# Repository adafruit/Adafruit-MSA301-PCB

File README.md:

## Adafruit MSA301 Triple Axis Accelerometer PCB

<a href="http://www.adafruit.com/products/4344"><br/>
Click here to purchase one from the Adafruit shop</a>

PCB files for the Adafruit MSA301 Triple Axis Accelerometer. 

Format is EagleCAD schematic and board layout
* https://www.adafruit.com/product/4344

### Description

The MSA301 is a super small and low cost **triple-axis accelerometer**. It's inexpensive, but has just about every 'extra' you'd want in an accelerometer:

* Three axis sensing, 14-bit resolution
* ±2g/±4g/±8g/±16g selectable scaling
* I2C interface on fixed I2C address 0x26
* Interrupt output
* Multiple data rate options 1 Hz to 500 Hz
* As low as 2uA current draw in low power mode (just the chip itself, not including any supporting circuitry)
* Tap, Double-tap, orientation & freefall detection
To make life easier so you can focus on your important work, we've taken the MSA301 and put it onto a breakout PCB along with support circuitry to let you use this little wonder with 3.3V (Feather/Raspberry Pi) or 5V (Arduino/ Metro328) logic levels. Additionally since it speaks I2C you can easily connect it up with two wires (plus power and ground!).  We've even included [SparkFun qwiic](https://www.sparkfun.com/qwiic) compatible [STEMMA QT](https://learn.adafruit.com/introducing-adafruit-stemma-qt) connectors for the I2C bus so **you don't even need to solder!** Just wire up to your favorite micro and you can use our [CircuitPython/Python](https://github.com/adafruit/Adafruit_CircuitPython_MSA301) or [Arduino drivers](https://github.com/adafruit/Adafruit_MSA301] to easily interface with the MSA301 and get motion measurements ASAP.

### License

Adafruit invests time and resources providing this open source design, please support Adafruit and open-source hardware by purchasing products from [Adafruit](https://www.adafruit.com)!

Designed by Limor Fried/Ladyada for Adafruit Industries.

Creative Commons Attribution/Share-Alike, all text above must be included in any redistribution. 
See license.txt for additional details.

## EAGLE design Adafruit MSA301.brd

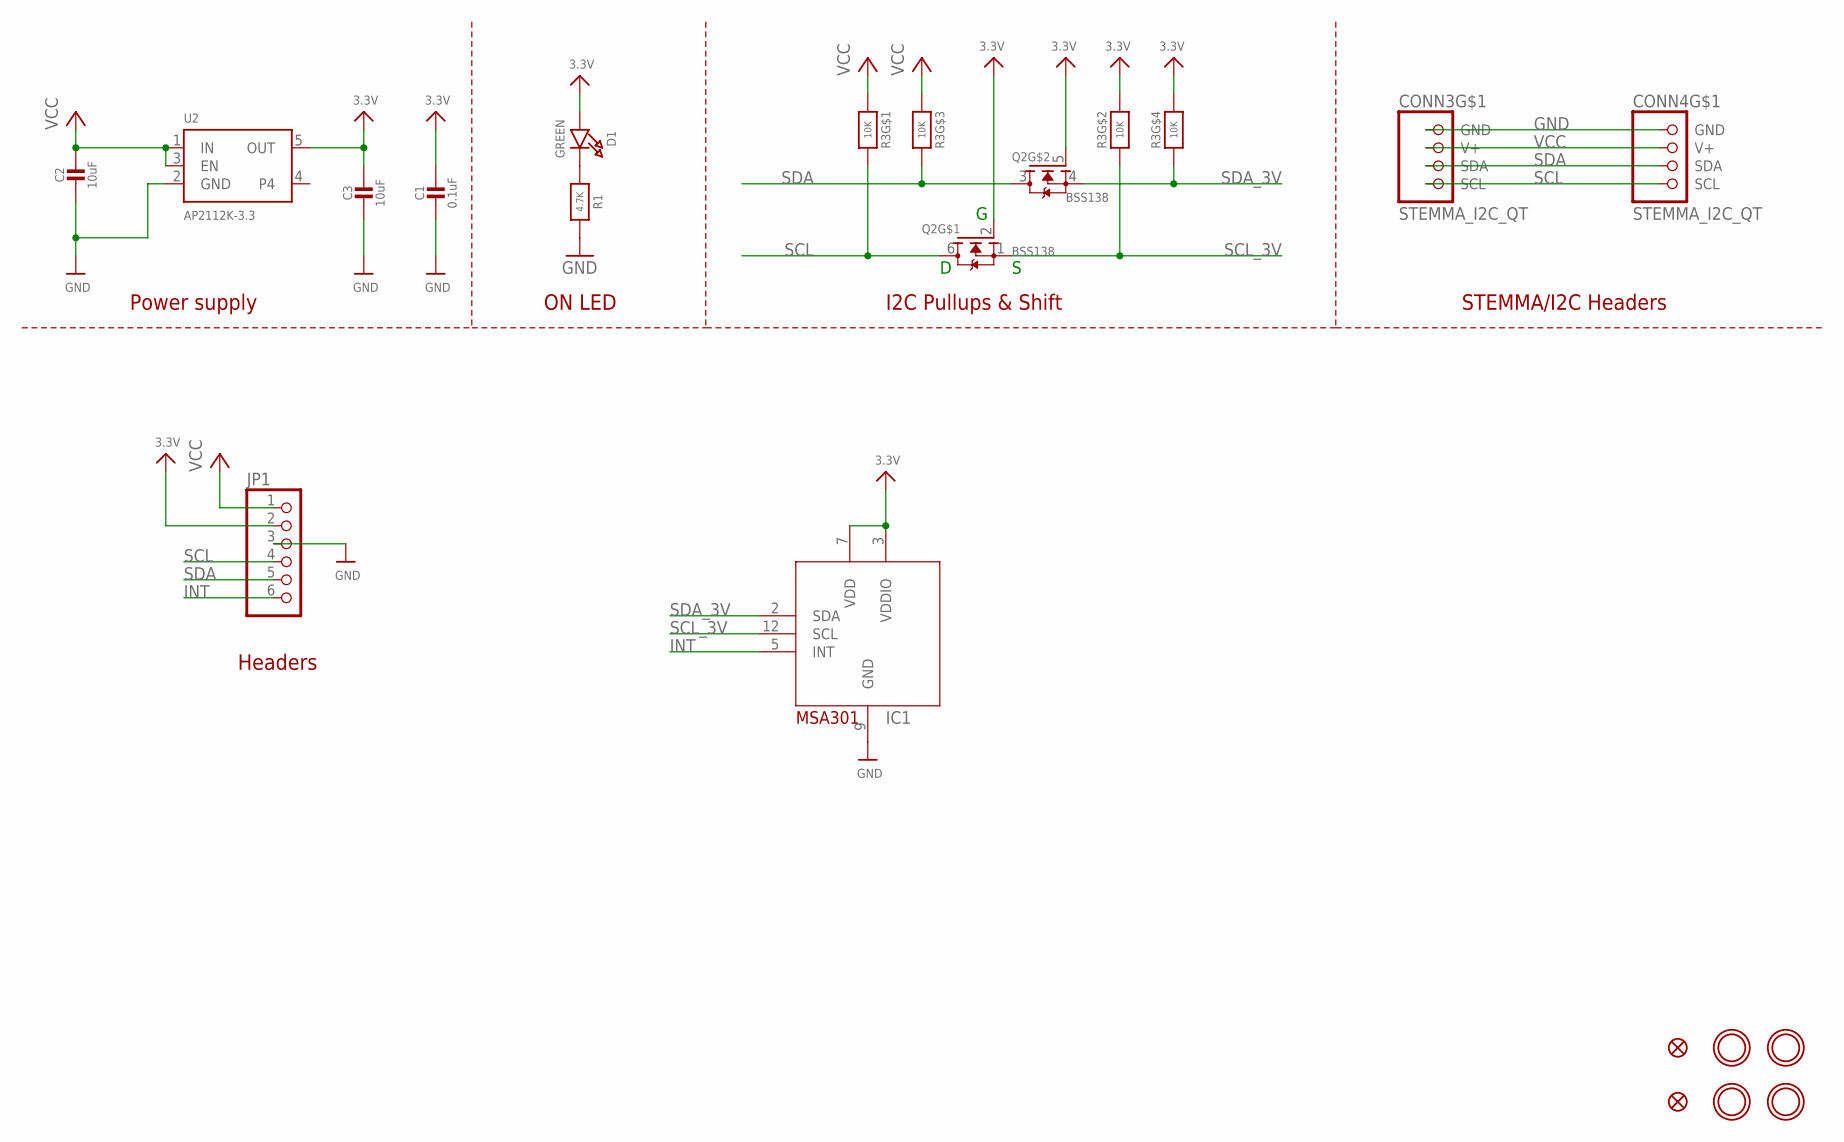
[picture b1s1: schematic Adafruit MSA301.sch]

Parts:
C1: 0.1uF; 0603-NO
C2, C3: 10uF; 0805-NO
CONN3, CONN4: STEMMA_I2C_QT; JST_SH4
D1: GREEN; CHIPLED_0603_NOOUTLINE
FID3, FID4: FIDUCIAL_1MM
IC1: MSA301; LGA12_2X2MM
JP1: HEADER-1X670MIL; 1X06_ROUND_70
Q2: BSS138; SOT363
R1: 4.7K; 0603-NO
R3: 10K; RESPACK_4X0603
U2: AP2112K-3.3; SOT23-5
U$1, U$17, U$19, U$21: MOUNTINGHOLE2.5; MOUNTINGHOLE_2.5_PLATED

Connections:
3.3V: C1.1, C3.1, D1.A, IC1.3 (VDDIO), IC1.7 (VDD), JP1.2, Q2.2 (G), Q2.5 (G), R3.2 (1), R3.4 (1), U2.5 (OUT)
GND: C1.2, C2.2, C3.2, CONN3.1 (GND), CONN4.1 (GND), IC1.9 (GND), JP1.3, R1.2, U2.2 (GND)
INT: IC1.5 (INT), JP1.6
unnamed: D1.C, R1.1
SCL: CONN3.4 (SCL), CONN4.4 (SCL), JP1.4, Q2.6 (D), R3.8 (2)
SCL_3V: IC1.12 (SCL), Q2.1 (S), R3.7 (2)
SDA: CONN3.3 (SDA), CONN4.3 (SDA), JP1.5, Q2.3 (D), R3.6 (2)
SDA_3V: IC1.2 (SDA), Q2.4 (S), R3.5 (2)
VCC: C2.1, CONN3.2 (V+), CONN4.2 (V+), JP1.1, R3.1, R3.3 (1), U2.1 (IN), U2.3 (EN)

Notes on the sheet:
Power supply
I2C Pullups & Shift
STEMMA/I2C Headers
Headers
ON LED

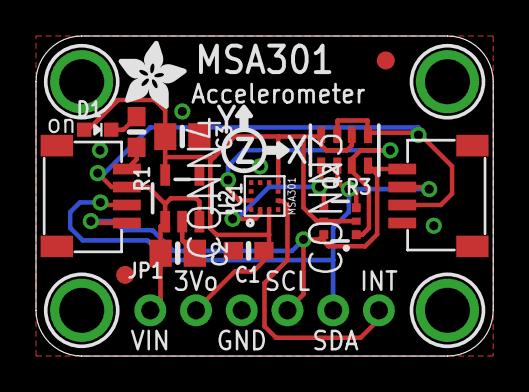
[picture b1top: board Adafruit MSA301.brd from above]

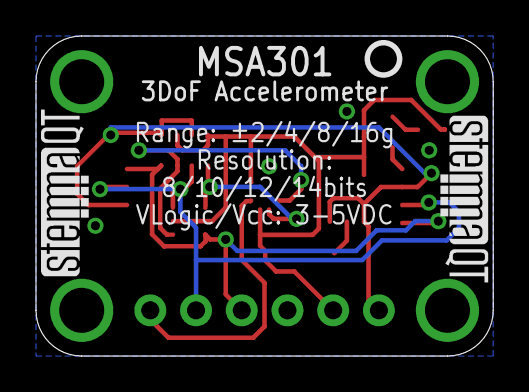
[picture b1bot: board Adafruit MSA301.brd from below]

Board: 2 copper layers, 25.4 x 17.8 mm, 22 parts (3 on the bottom side), 9 nets.

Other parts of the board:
U$22: ADAFRUIT_3.5MM
U$25: PCBFEAT-REV-040
U$30, U$31: STEMMAQT

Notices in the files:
parts and their libraries:
microbuilder: This work is placed in the public domain, and may be freely used for commercial and non-commercial work with the following conditions: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
